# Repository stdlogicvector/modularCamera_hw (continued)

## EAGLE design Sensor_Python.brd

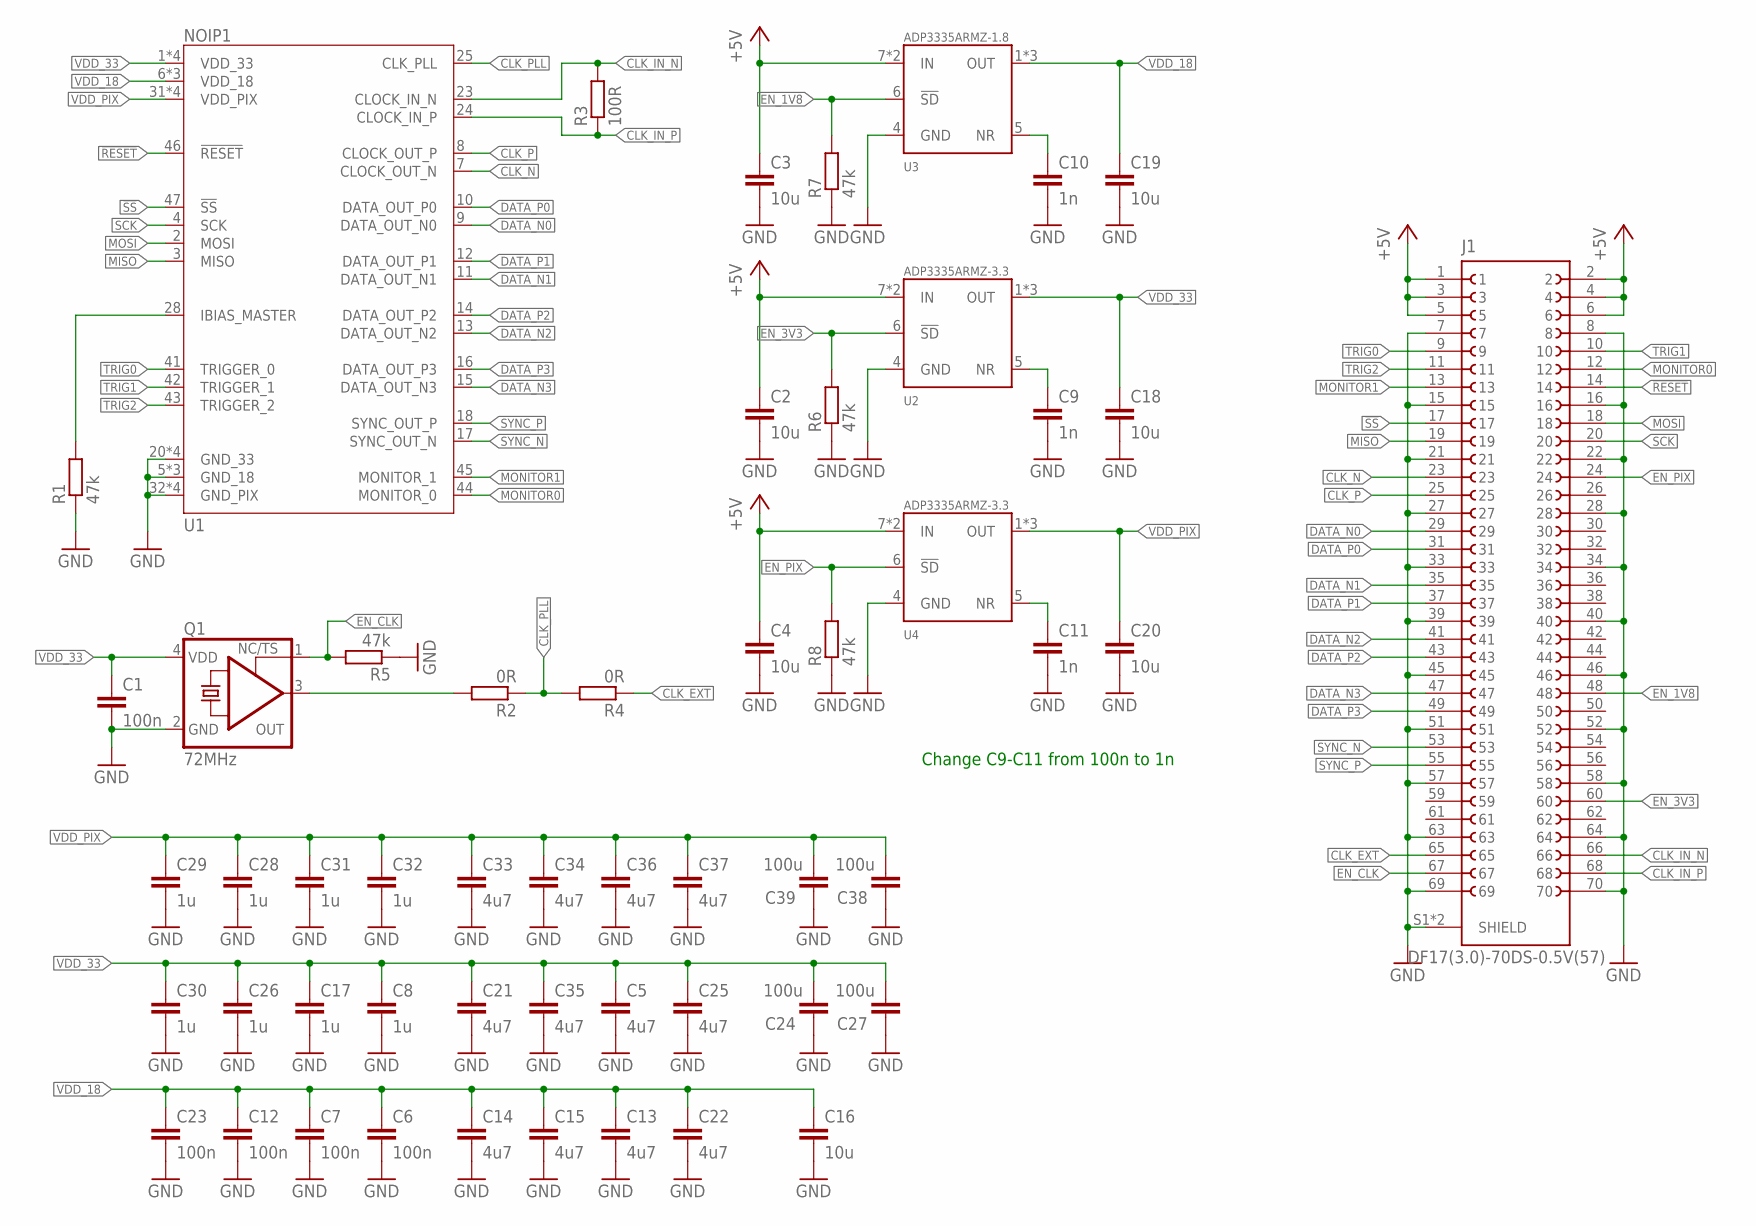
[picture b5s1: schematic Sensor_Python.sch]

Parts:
C1, C6, C7, C12, C23: 100n; C0402; LCSC C1525
C2, C3, C4, C16, C18, C19, C20: 10u; C0603
C5, C13, C14, C15, C21, C22, C25, C33, C34, C35, C36, C37: 4u7; C0603; LCSC C19666
C8, C17, C26, C28, C29, C30, C31, C32: 1u; C0402
C9, C10, C11: 1n; C0402; LCSC C1525
C24, C27, C38, C39: 100u; C1206; DIGIKEY 490-GRM31CD80J107MEA8LCT-ND
J1: DF17(3.0)-70DS-0.5V(57)
Q1: 72MHz; 3.2X2.5_KXO-V96; DIGIKEY 1473-SIT8208AC-23-33E-72.000000-ND
R1, R5, R6, R7, R8: 47k; R0402
R2, R4: 0R; R0402
R3: 100R; R0402
U1: NOIP1; LCC-44
U2, U4: ADP3335ARMZ-3.3; MSOP08; DIGIKEY 505-ADP3335ARMZ-3.3RL7CT-ND
U3: ADP3335ARMZ-1.8; MSOP08; DIGIKEY 505-ADP3335ARMZ-1.8-R7CT-ND

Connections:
!RESET: J1.14, U1.46 (!RESET)
!SS: J1.17, U1.47 (!SS)
+5V: C2.1, C3.1, C4.1, J1.1, J1.2, J1.3, J1.4, J1.5, J1.6, U2.7 (IN), U2.8 (IN), U3.7 (IN), U3.8 (IN), U4.7 (IN), U4.8 (IN)
CLK: Q1.3 (OUT), R2.2
CLK_EXT: J1.65, R4.1
CLK_IN_N: J1.66, R3.2, U1.23 (CLOCK_IN_N)
CLK_IN_P: J1.68, R3.1, U1.24 (CLOCK_IN_P)
CLK_N: J1.23, U1.7 (CLOCK_OUT_N)
CLK_P: J1.25, U1.8 (CLOCK_OUT_P)
CLK_PLL: R2.1, R4.2, U1.25 (CLK_PLL)
DATA_N0: J1.29, U1.9 (DATA_OUT_N0)
DATA_N1: J1.35, U1.11 (DATA_OUT_N1)
DATA_N2: J1.41, U1.13 (DATA_OUT_N2)
DATA_N3: J1.47, U1.15 (DATA_OUT_N3)
DATA_P0: J1.31, U1.10 (DATA_OUT_P0)
DATA_P1: J1.37, U1.12 (DATA_OUT_P1)
DATA_P2: J1.43, U1.14 (DATA_OUT_P2)
DATA_P3: J1.49, U1.16 (DATA_OUT_P3)
EN_1V8: J1.48, R7.2, U3.6 (!SD)
EN_3V3: J1.60, R6.2, U2.6 (!SD)
EN_CLK: J1.67, Q1.1 (TS), R5.2
EN_PIX: J1.24, R8.2, U4.6 (!SD)
GND: C1.2, C2.2, C3.2, C4.2, C5.2, C6.2, C7.2, C8.2, C9.2, C10.2, C11.2, C12.2, C13.2, C14.2, C15.2, C16.2, C17.2, C18.2, C19.2, C20.2, C21.2, C22.2, C23.2, C24.2, C25.2, C26.2, C27.2, C28.2, C29.2, C30.2, C31.2, C32.2, C33.2, C34.2, C35.2, C36.2, C37.2, C38.2, C39.2, J1.7, J1.8, J1.15, J1.16, J1.21, J1.22, J1.27, J1.28, J1.33, J1.34, J1.39, J1.40, J1.45, J1.46, J1.51, J1.52, J1.57, J1.58, J1.63, J1.64, J1.69, J1.70, J1.S1 (SHIELD), J1.S2 (SHIELD), Q1.2 (GND), R1.1, R5.1, R6.1, R7.1, R8.1, U1.5 (GND_18), U1.20 (GND_33), U1.21 (GND_18), U1.27 (GND_18), U1.30 (GND_33), U1.32 (GND_PIX), U1.34 (GND_PIX), U1.35 (GND_33), U1.37 (GND_PIX), U1.39 (GND_PIX), U1.48 (GND_33), U2.4 (GND), U3.4 (GND), U4.4 (GND)
MISO: J1.19, U1.3 (MISO)
MONITOR0: J1.12, U1.44 (MONITOR_0)
MONITOR1: J1.13, U1.45 (MONITOR_1)
MOSI: J1.18, U1.2 (MOSI)
unnamed: R1.2, U1.28 (IBIAS_MASTER)
unnamed: C11.1, U4.5 (NR)
unnamed: C10.1, U3.5 (NR)
unnamed: C9.1, U2.5 (NR)
SCK: J1.20, U1.4 (SCK)
SYNC_N: J1.53, U1.17 (SYNC_OUT_N)
SYNC_P: J1.55, U1.18 (SYNC_OUT_P)
TRIG0: J1.9, U1.41 (TRIGGER_0)
TRIG1: J1.10, U1.42 (TRIGGER_1)
TRIG2: J1.11, U1.43 (TRIGGER_2)
VDD_18: C6.1, C7.1, C12.1, C13.1, C14.1, C15.1, C16.1, C19.1, C22.1, C23.1, U1.6 (VDD_18), U1.22 (VDD_18), U1.26 (VDD_18), U3.1 (OUT), U3.2 (OUT), U3.3 (OUT)
VDD_33: C1.1, C5.1, C8.1, C17.1, C18.1, C21.1, C24.1, C25.1, C26.1, C27.1, C30.1, C35.1, Q1.4 (VDD), U1.1 (VDD_33), U1.19 (VDD_33), U1.29 (VDD_33), U1.36 (VDD_33), U2.1 (OUT), U2.2 (OUT), U2.3 (OUT)
VDD_PIX: C20.1, C28.1, C29.1, C31.1, C32.1, C33.1, C34.1, C36.1, C37.1, C38.1, C39.1, U1.31 (VDD_PIX), U1.33 (VDD_PIX), U1.38 (VDD_PIX), U1.40 (VDD_PIX), U4.1 (OUT), U4.2 (OUT), U4.3 (OUT)

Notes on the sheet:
Change C9-C11 from 100n to 1n

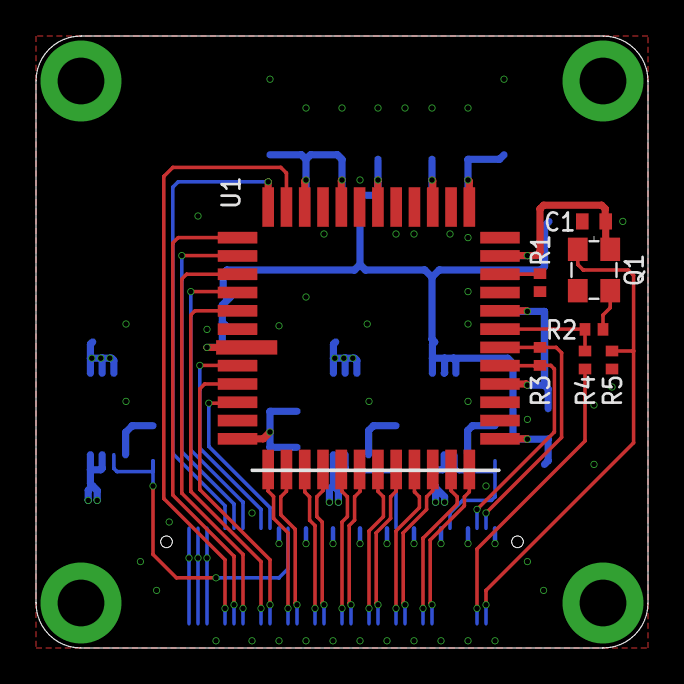
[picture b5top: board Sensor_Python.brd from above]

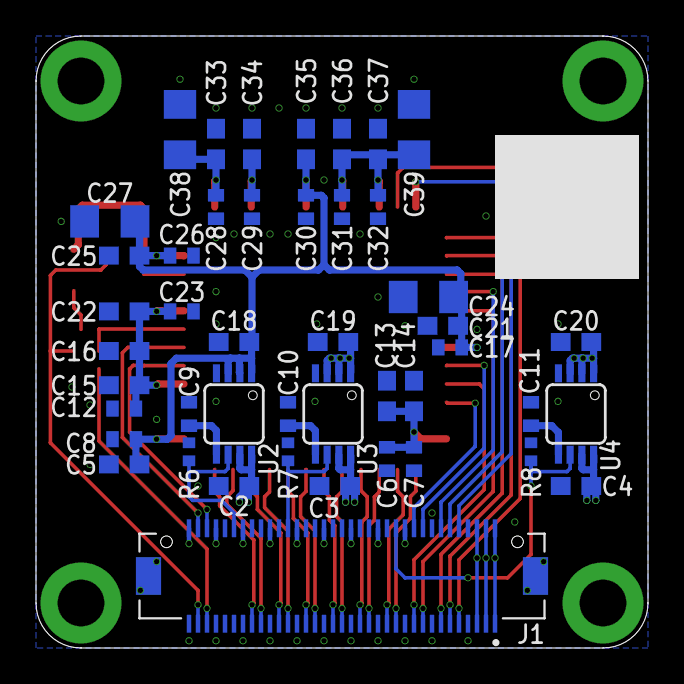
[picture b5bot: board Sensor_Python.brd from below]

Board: 4 copper layers, 34.0 x 34.0 mm, 53 parts (45 on the bottom side), 40 nets.
